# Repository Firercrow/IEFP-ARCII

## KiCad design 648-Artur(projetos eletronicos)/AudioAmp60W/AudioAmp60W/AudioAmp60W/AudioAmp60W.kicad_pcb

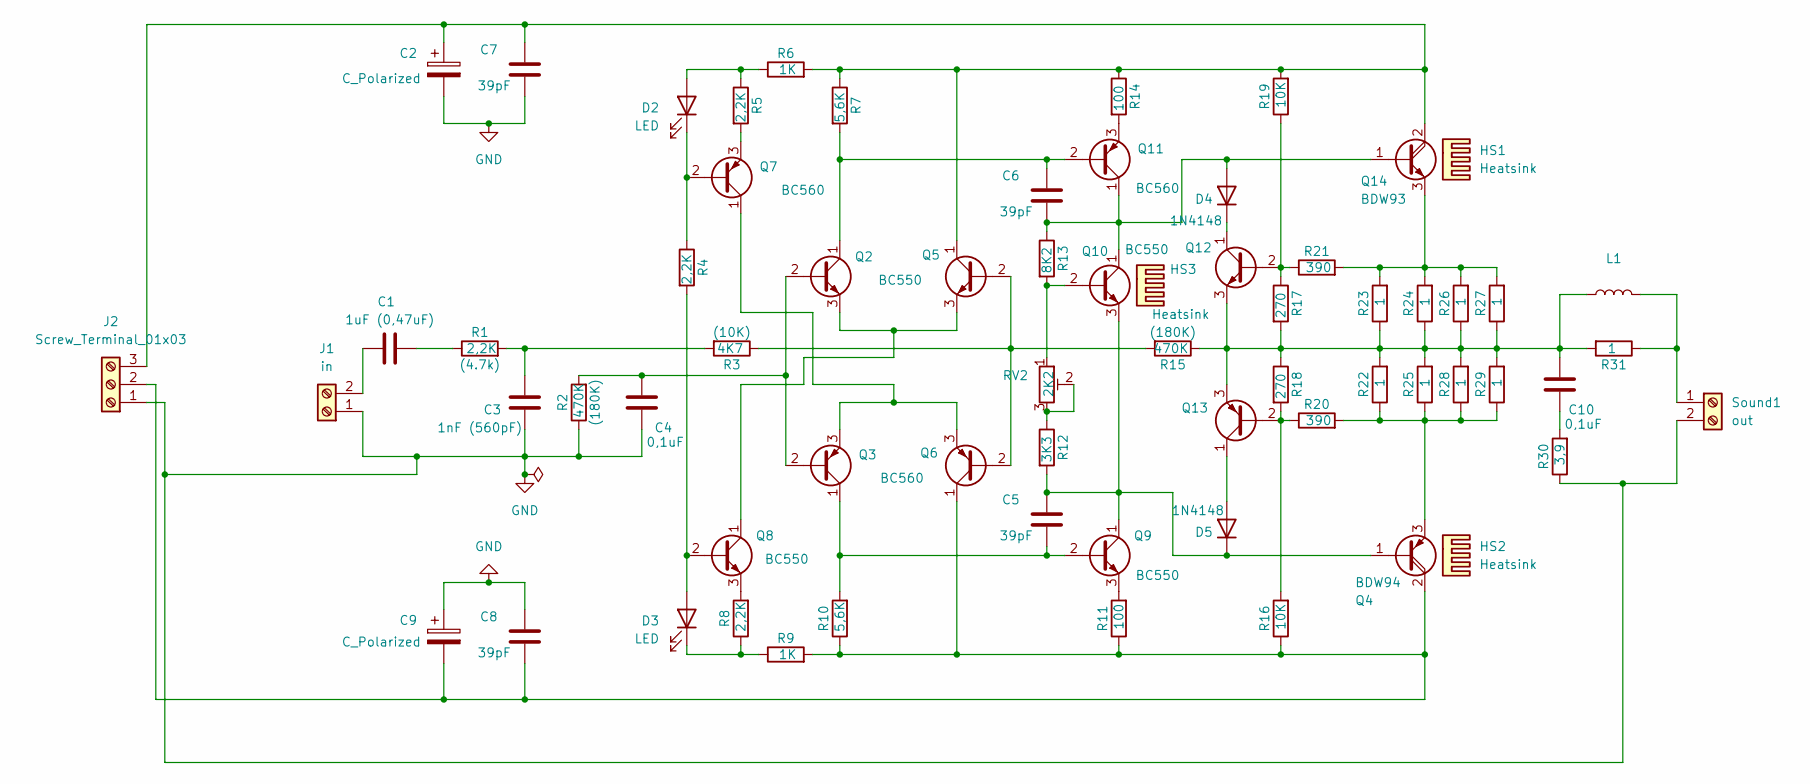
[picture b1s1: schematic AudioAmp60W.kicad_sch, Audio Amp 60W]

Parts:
C1: 1uF (0,47uF); C_Rect_L4.6mm_W2.0mm_P2.50mm_MKS02_FKP02
C2, C9: C_Polarized; CP_Radial_D4.0mm_P1.50mm
C3: 1nF (560pF); C_Rect_L4.6mm_W2.0mm_P2.50mm_MKS02_FKP02
C4, C10: 0,1uF; C_Rect_L4.6mm_W2.0mm_P2.50mm_MKS02_FKP02
C5, C6, C7, C8: 39pF; C_Rect_L4.6mm_W2.0mm_P2.50mm_MKS02_FKP02
D2, D3: LED; LED_Rectangular_W3.0mm_H2.0mm
D4, D5: 1N4148; D_DO-35_SOD27_P7.62mm_Horizontal
HS1, HS2, HS3: Heatsink
J1: in; TerminalBlock_Phoenix_MKDS-1-2-3.81_1x02_P3.81mm_Horizontal
J2: Screw_Terminal_01x03; TerminalBlock_Phoenix_MKDS-1-3-3.81_1x03_P3.81mm_Horizontal
L1: L_Axial_L7.0mm_D3.3mm_P10.16mm_Horizontal_Fastron_MICC
Q2, Q5, Q8, Q9, Q10, Q12: BC550; TO-92_Inline
Q3, Q6, Q7, Q11, Q13: BC560; TO-92_Inline
Q4: BDW94; TO-220-3_Vertical
Q14: BDW93; TO-220-3_Vertical
R1, R4, R5, R8: 2,2K; R_Axial_DIN0204_L3.6mm_D1.6mm_P7.62mm_Horizontal
R2, R15: 470K; R_Axial_DIN0204_L3.6mm_D1.6mm_P7.62mm_Horizontal
R3: 4K7; R_Axial_DIN0204_L3.6mm_D1.6mm_P7.62mm_Horizontal
R6, R9: 1K; R_Axial_DIN0204_L3.6mm_D1.6mm_P7.62mm_Horizontal
R7, R10: 5,6K; R_Axial_DIN0204_L3.6mm_D1.6mm_P7.62mm_Horizontal
R11, R14: 100; R_Axial_DIN0204_L3.6mm_D1.6mm_P7.62mm_Horizontal
R12: 3K3; R_Axial_DIN0204_L3.6mm_D1.6mm_P7.62mm_Horizontal
R13: 8K2; R_Axial_DIN0204_L3.6mm_D1.6mm_P7.62mm_Horizontal
R16, R19: 10K; R_Axial_DIN0204_L3.6mm_D1.6mm_P7.62mm_Horizontal
R17, R18: 270; R_Axial_DIN0204_L3.6mm_D1.6mm_P7.62mm_Horizontal
R20, R21: 390; R_Axial_DIN0204_L3.6mm_D1.6mm_P7.62mm_Horizontal
R22, R23, R24, R25, R26, R27, R28, R29, R31: 1; R_Axial_DIN0204_L3.6mm_D1.6mm_P7.62mm_Horizontal
R30: 3,9; R_Axial_DIN0204_L3.6mm_D1.6mm_P7.62mm_Horizontal
RV2: 2K2; Potentiometer_Bourns_3266W_Vertical
Sound1: out; TerminalBlock_Phoenix_MKDS-1-2-3.81_1x02_P3.81mm_Horizontal

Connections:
GND: C2.2, C3.2, C4.2, C7.2, C8.1, C9.1, J1.1, J2.1, R2.1, R30.1, Sound1.2
unnamed: C1.1, R1.1
unnamed: C3.1, R1.2, R3.2
unnamed: C10.2, R30.2
unnamed: D2.2 (A), R5.1, R6.1
unnamed: D2.1 (K), Q7.2 (B), R4.1
unnamed: D3.2 (A), Q8.2 (B), R4.2
unnamed: D3.1 (K), R8.1, R9.1
unnamed: C6.2, D4.2 (A), Q10.1 (C), Q11.1 (C), Q14.1 (B), R13.1
unnamed: D4.1 (K), Q12.1 (C)
unnamed: D5.2 (A), Q13.1 (C)
unnamed: C5.1, D5.1 (K), Q4.1 (B), Q9.1 (C), Q10.3 (E), R12.2
unnamed: C1.2, J1.2
unnamed: C8.2, C9.2, J2.2, Q4.2 (C), Q6.1 (C), R9.2, R10.1, R11.1, R16.1
unnamed: C2.1, C7.1, J2.3, Q5.1 (C), Q14.2 (C), R6.2, R7.1, R14.1, R19.2
unnamed: C4.1, Q2.2 (B), Q3.2 (B), R2.2
unnamed: Q2.3 (E), Q5.3 (E), Q8.1 (C)
unnamed: C5.2, Q3.1 (C), Q9.2 (B), R10.2
unnamed: Q3.3 (E), Q6.3 (E), Q7.1 (C)
unnamed: Q4.3 (E), R20.2, R22.1, R25.1, R28.1, R29.1
unnamed: Q5.2 (B), Q6.2 (B), R3.1, R15.2
unnamed: Q7.3 (E), R5.2
unnamed: Q8.3 (E), R8.2
unnamed: Q9.3 (E), R11.2
unnamed: Q10.2 (B), R13.2, RV2.1
unnamed: C6.1, Q2.1 (C), Q11.2 (B), R7.2
unnamed: Q11.3 (E), R14.2
unnamed: Q12.2 (B), R17.1, R19.1, R21.1
unnamed: C10.1, L1.1, Q12.3 (E), Q13.3 (E), R15.1, R17.2, R18.1, R22.2, R23.1, R24.1, R25.2, R26.1, R27.1, R28.2, R29.2, R31.2
unnamed: Q13.2 (B), R16.2, R18.2, R20.1
unnamed: Q14.3 (E), R21.2, R23.2, R24.2, R26.2, R27.2
unnamed: R12.1, RV2.2, RV2.3
unnamed: L1.2, R31.1, Sound1.1

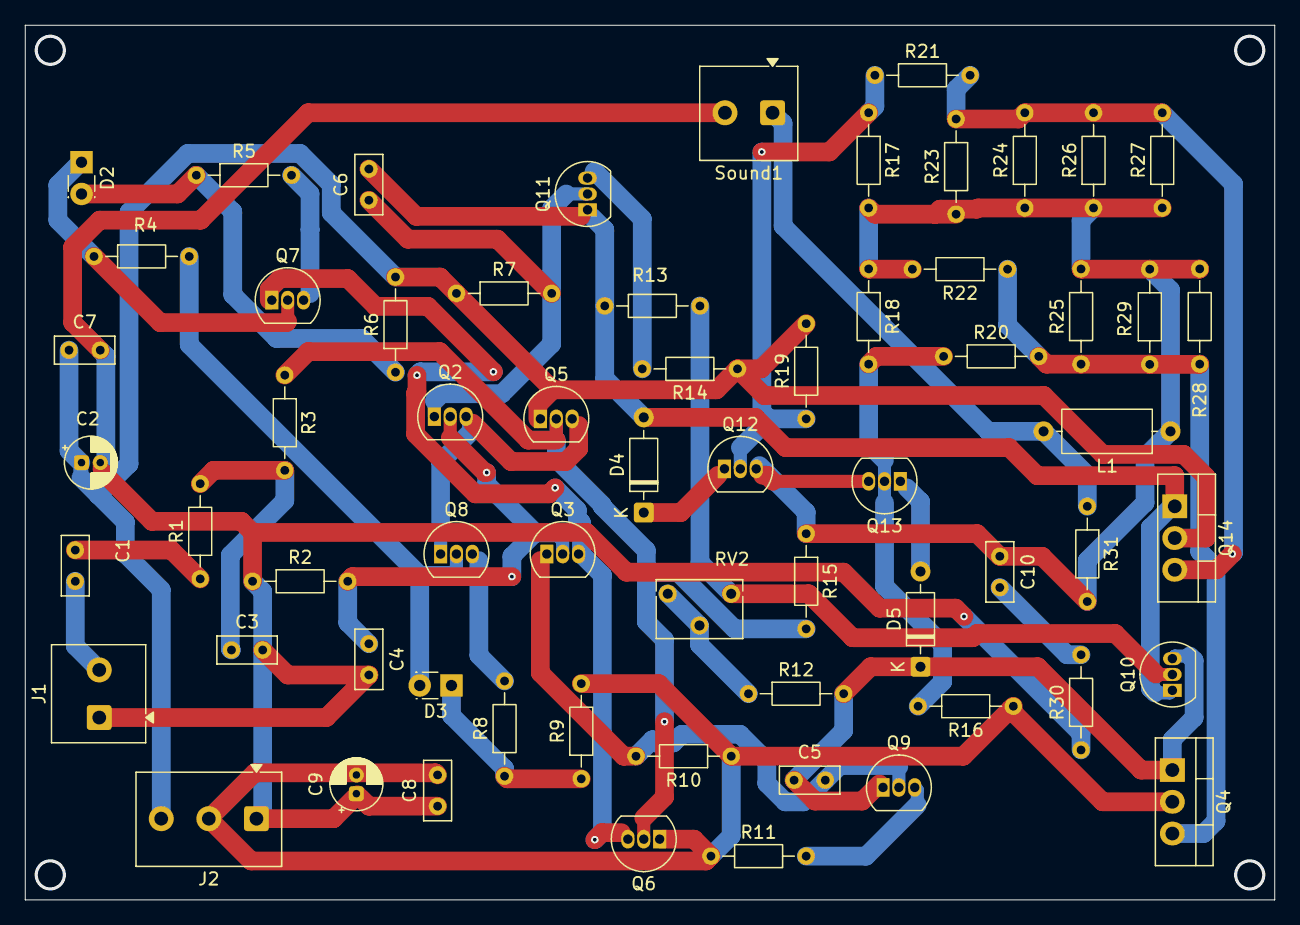
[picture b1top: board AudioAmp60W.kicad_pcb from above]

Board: 2 copper layers, 100.0 x 70.0 mm, 63 parts (0 on the bottom side), 33 nets.

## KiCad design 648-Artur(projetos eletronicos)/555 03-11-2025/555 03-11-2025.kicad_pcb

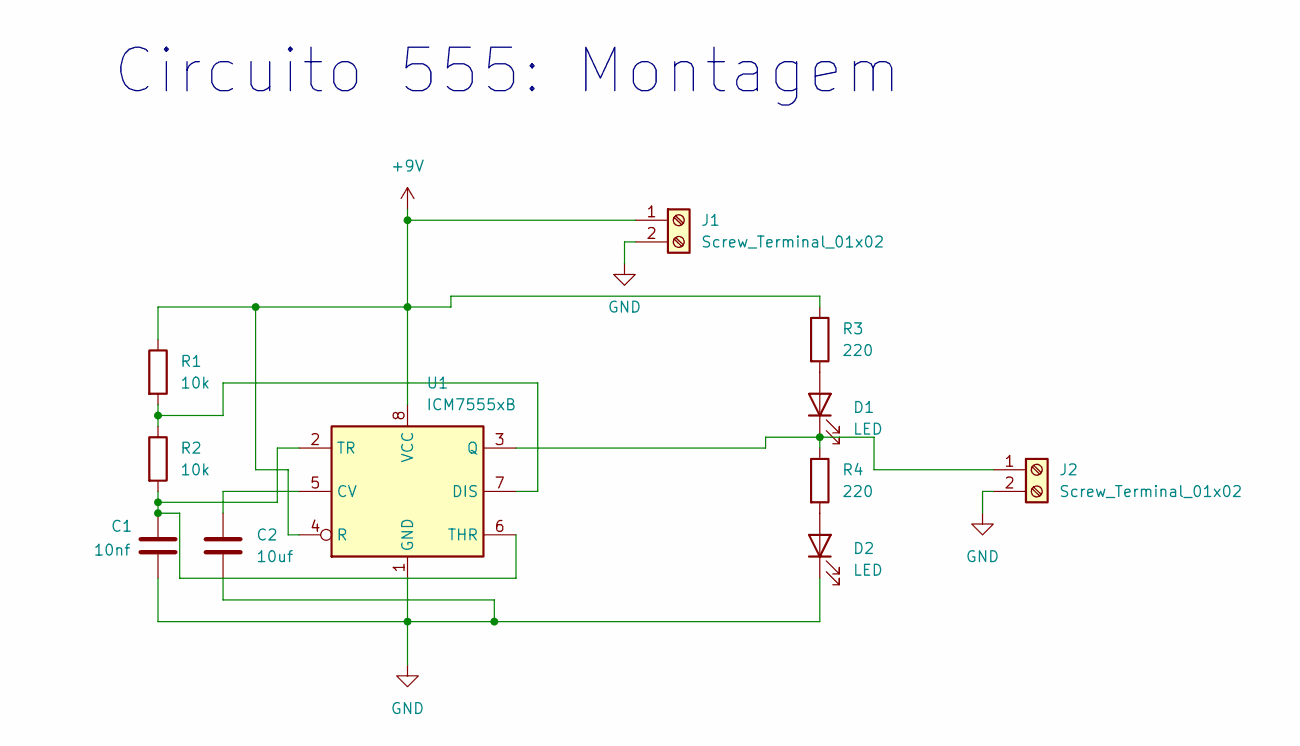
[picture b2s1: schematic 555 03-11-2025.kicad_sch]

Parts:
C1: 10nf; C_Radial_D4.0mm_H5.0mm_P1.50mm
C2: 10uf; C_Disc_D4.3mm_W1.9mm_P5.00mm
D1, D2: LED; LED_D3.0mm_Clear
J1, J2: Screw_Terminal_01x02; TerminalBlock_Philmore_TB132_1x02_P5.00mm_Horizontal
R1, R2: 10k; R_Axial_DIN0204_L3.6mm_D1.6mm_P5.08mm_Horizontal
R3, R4: 220; R_Axial_DIN0204_L3.6mm_D1.6mm_P7.62mm_Horizontal
U1: ICM7555xB; DIP-8_W7.62mm

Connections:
+9V: J1.1, R1.1, R3.1, U1.4 (R), U1.8 (VCC)
GND: C1.2, C2.2, D2.1 (K), J1.2, J2.2, U1.1 (GND)
unnamed: D1.2 (A), R3.2
unnamed: D1.1 (K), J2.1, R4.1, U1.3 (Q)
unnamed: D2.2 (A), R4.2
unnamed: C2.1, U1.5 (CV)
unnamed: R1.2, R2.1, U1.7 (DIS)
unnamed: C1.1, R2.2, U1.2 (TR), U1.6 (THR)

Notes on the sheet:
Circuito 555: Montagem

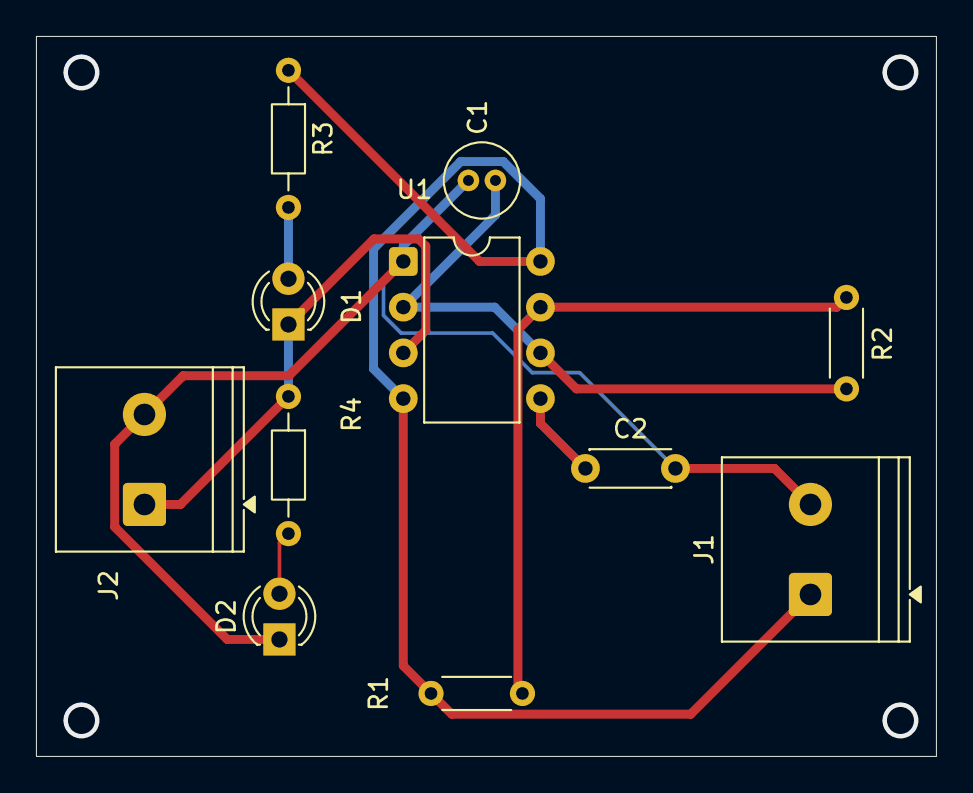
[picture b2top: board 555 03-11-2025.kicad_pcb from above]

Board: 2 copper layers, 50.0 x 40.0 mm, 11 parts (0 on the bottom side), 8 nets.

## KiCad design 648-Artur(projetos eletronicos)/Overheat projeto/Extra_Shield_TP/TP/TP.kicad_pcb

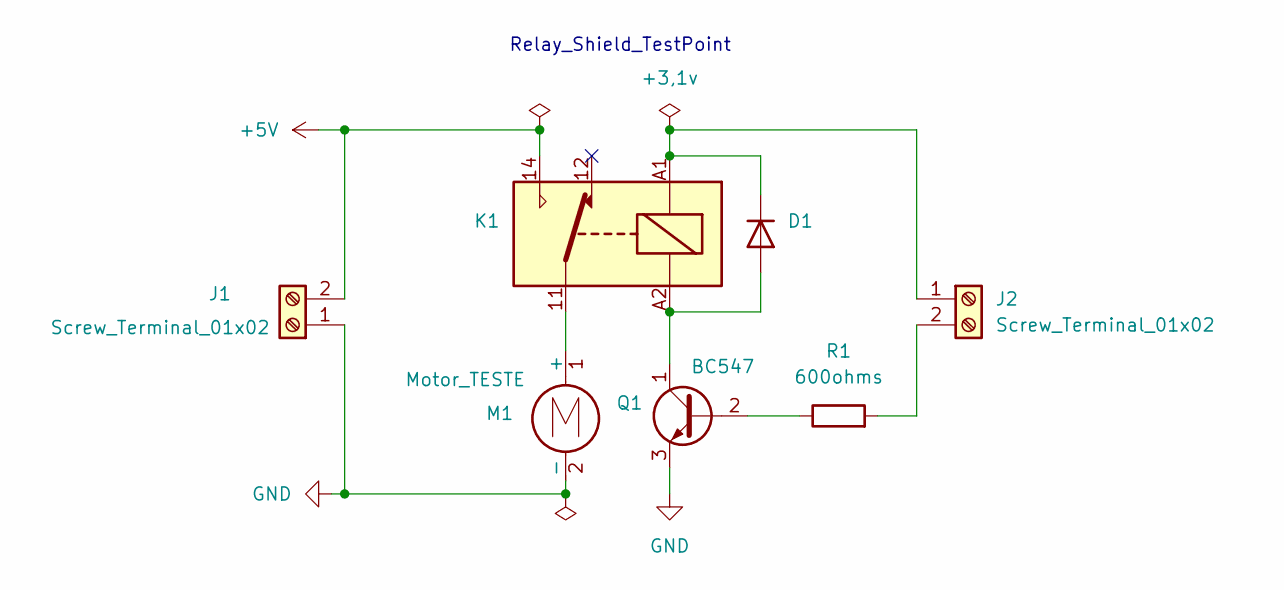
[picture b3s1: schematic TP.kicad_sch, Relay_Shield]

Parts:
D1: 1N4148WT; D_5W_P10.16mm_Horizontal
J1: Screw_Terminal_01x02; TerminalBlock_Phoenix_MKDS-1-2-3.81_1x02_P3.81mm_Horizontal
J2: Screw_Terminal_01x02; TerminalBlock_Phoenix_PT-1,5-2-3.5-H_1x02_P3.50mm_Horizontal
K1: Fujitsu_FTR-LYCA005x; Relay_SPDT_Schrack-RT1-FormC_RM5mm
M1: Motor_TESTE; TerminalBlock_Xinya_XY308-2.54-2P_1x02_P2.54mm_Horizontal
Q1: BC547; TO-92_Inline
R1: 600ohms; R_Axial_DIN0204_L3.6mm_D1.6mm_P5.08mm_Horizontal

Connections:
+5V: J1.2, K1.14
GND: J1.1, M1.2 (-), Q1.3 (E)
unnamed: D1.2 (A), K1.A2, Q1.1 (C)
unnamed: D1.1 (K), J2.1, K1.A1
unnamed: J2.2, R1.2
unnamed: K1.11, M1.1 (+)
unnamed: Q1.2 (B), R1.1

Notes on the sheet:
Relay_Shield_TestPoint

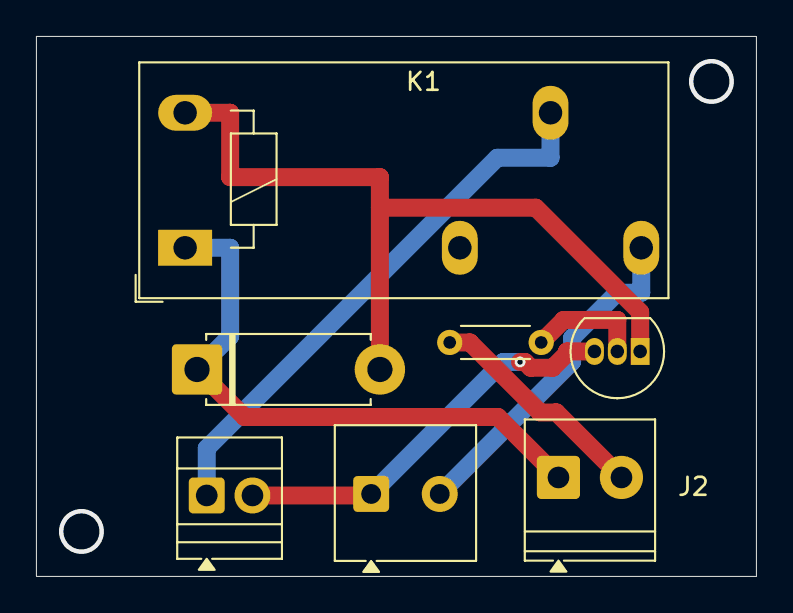
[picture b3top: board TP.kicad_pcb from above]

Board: 2 copper layers, 40.0 x 30.0 mm, 7 parts (0 on the bottom side), 7 nets.

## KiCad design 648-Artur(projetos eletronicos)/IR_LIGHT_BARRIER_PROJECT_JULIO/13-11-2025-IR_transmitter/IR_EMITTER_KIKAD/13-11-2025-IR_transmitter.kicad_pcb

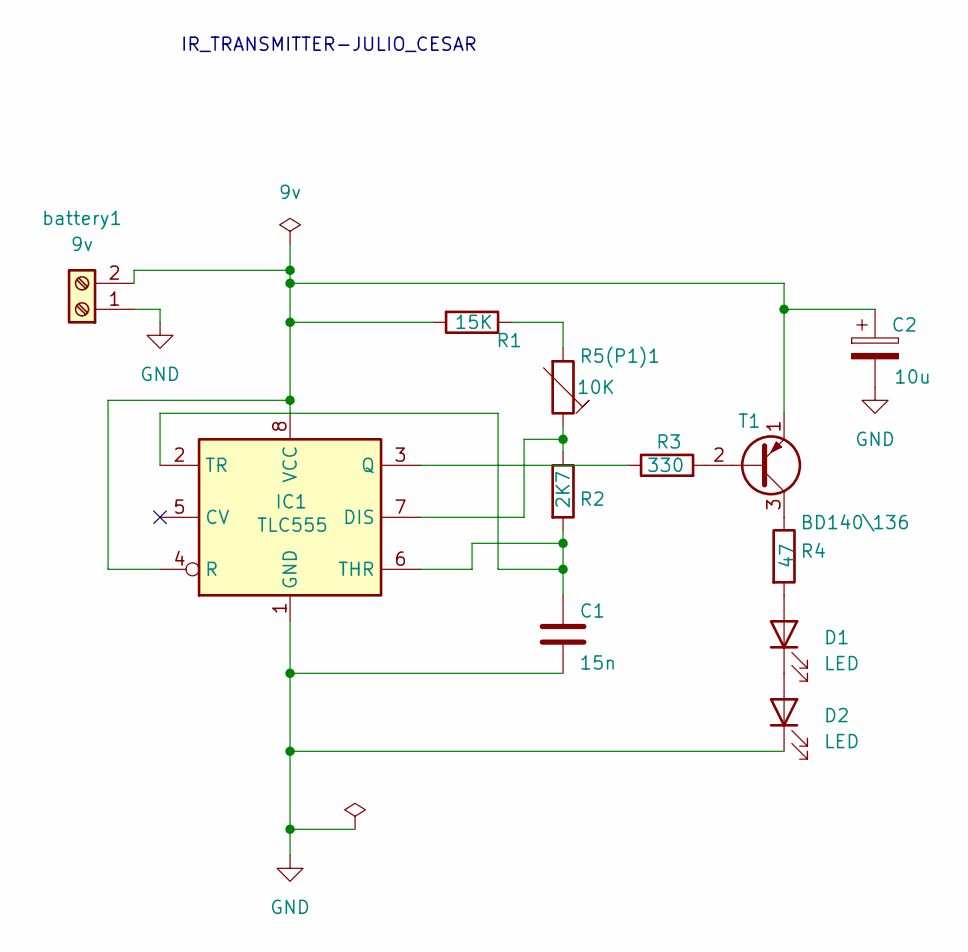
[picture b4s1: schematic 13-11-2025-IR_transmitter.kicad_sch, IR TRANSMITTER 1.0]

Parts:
C1: 15n; C_Rect_L4.0mm_W2.5mm_P2.50mm
C2: 10u; CP_Radial_D5.0mm_P2.50mm
D1, D2: LED; LED_D3.0mm
IC1: TLC555; DIP-8_W7.62mm
R1: 15K; R_Axial_DIN0204_L3.6mm_D1.6mm_P5.08mm_Horizontal
R2: 2K7; R_Axial_DIN0204_L3.6mm_D1.6mm_P5.08mm_Horizontal
R3: 330; R_Axial_DIN0204_L3.6mm_D1.6mm_P7.62mm_Horizontal
R4: 47; R_Axial_DIN0204_L3.6mm_D1.6mm_P5.08mm_Horizontal
R5(P1)1: 10K; R_Axial_DIN0204_L3.6mm_D1.6mm_P5.08mm_Horizontal
T1: BD140\136; TO-92_Inline
battery1: 9v; TerminalBlock_Phoenix_MPT-0,5-2-2.54_1x02_P2.54mm_Horizontal

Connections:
+9V: C2.1, IC1.4 (R), IC1.8 (VCC), R1.2, T1.1 (E), battery1.2
GND: C1.2, C2.2, D2.1 (K), IC1.1 (GND), battery1.1
unnamed: D1.2 (A), R4.2
unnamed: D1.1 (K), D2.2 (A)
unnamed: IC1.7 (DIS), R2.1, R5(P1)1.1
unnamed: IC1.3 (Q), R3.1
unnamed: C1.1, IC1.2 (TR), IC1.6 (THR), R2.2
unnamed: R1.1, R5(P1)1.2
unnamed: R3.2, T1.2 (B)
unnamed: R4.1, T1.3 (C)

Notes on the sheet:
IR_TRANSMITTER-JULIO_CESAR

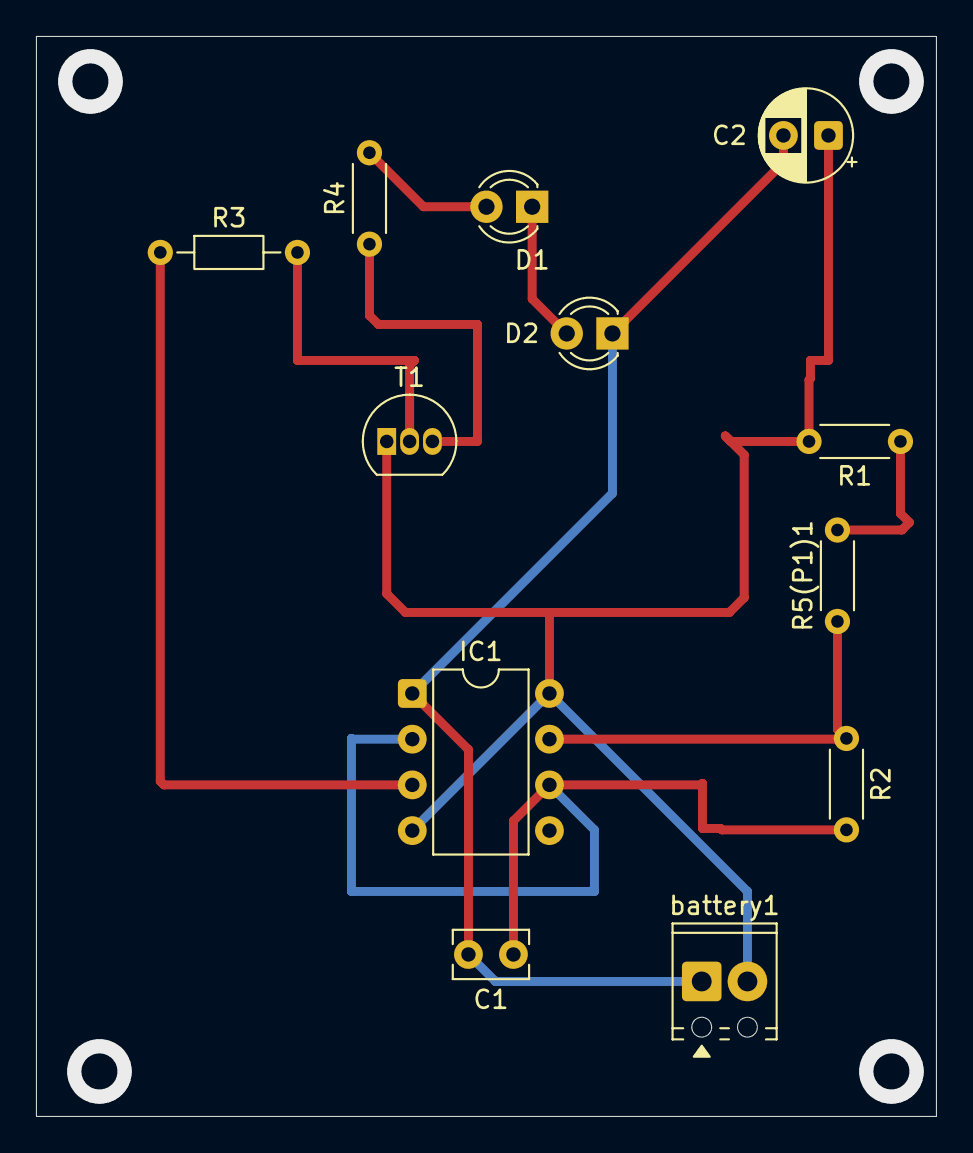
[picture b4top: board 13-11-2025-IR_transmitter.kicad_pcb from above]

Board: 2 copper layers, 50.0 x 60.0 mm, 12 parts (0 on the bottom side), 10 nets.

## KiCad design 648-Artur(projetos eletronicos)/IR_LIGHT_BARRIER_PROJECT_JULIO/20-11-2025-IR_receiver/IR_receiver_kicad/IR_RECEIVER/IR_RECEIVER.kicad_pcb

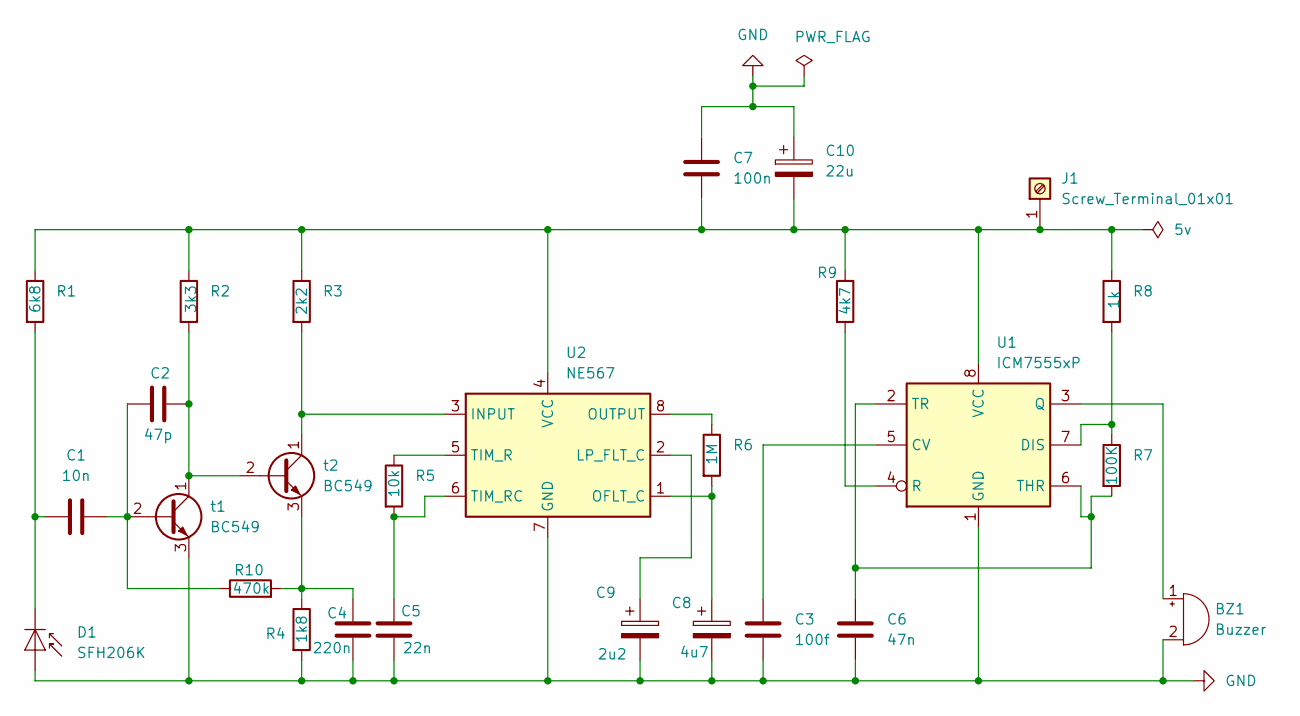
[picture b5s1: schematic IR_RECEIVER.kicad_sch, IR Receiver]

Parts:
BZ1: Buzzer; Buzzer_12x9.5RM7.6
C1: 10n; C_Rect_L4.6mm_W3.8mm_P2.50mm_MKS02_FKP02
C2: 47p; C_Rect_L4.6mm_W3.8mm_P2.50mm_MKS02_FKP02
C3: 100f; C_Rect_L4.6mm_W3.8mm_P2.50mm_MKS02_FKP02
C4: 220n; C_Rect_L4.6mm_W3.8mm_P2.50mm_MKS02_FKP02
C5: 22n; C_Rect_L4.6mm_W3.8mm_P2.50mm_MKS02_FKP02
C6: 47n; C_Rect_L4.6mm_W3.8mm_P2.50mm_MKS02_FKP02
C7: 100n; C_Rect_L4.6mm_W3.8mm_P2.50mm_MKS02_FKP02
C8: 4u7; CP_Radial_D4.0mm_P1.50mm
C9: 2u2; CP_Radial_D4.0mm_P1.50mm
C10: 22u; CP_Radial_D4.0mm_P1.50mm
D1: SFH206K; Osram_SFH205
J1: Screw_Terminal_01x01; TerminalBlock_MetzConnect_360272_1x01_Horizontal_ScrewM2.6
R1: 6k8; R_Axial_DIN0309_L9.0mm_D3.2mm_P12.70mm_Horizontal
R2: 3k3; R_Axial_DIN0309_L9.0mm_D3.2mm_P12.70mm_Horizontal
R3: 2k2; R_Axial_DIN0309_L9.0mm_D3.2mm_P12.70mm_Horizontal
R4: 1k8; R_Axial_DIN0309_L9.0mm_D3.2mm_P12.70mm_Horizontal
R5: 10k; R_Axial_DIN0309_L9.0mm_D3.2mm_P12.70mm_Horizontal
R6: 1M; R_Axial_DIN0309_L9.0mm_D3.2mm_P12.70mm_Horizontal
R7: 100K; R_Axial_DIN0309_L9.0mm_D3.2mm_P12.70mm_Horizontal
R8: 1k; R_Axial_DIN0309_L9.0mm_D3.2mm_P12.70mm_Horizontal
R9: 4k7; R_Axial_DIN0309_L9.0mm_D3.2mm_P12.70mm_Horizontal
R10: 470k; R_Axial_DIN0309_L9.0mm_D3.2mm_P12.70mm_Horizontal
U1: ICM7555xP; DIP-8_W7.62mm
U2: NE567; DIP-8_W7.62mm
t1, t2: BC549; TO-92_Inline

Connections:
GND: BZ1.2 (-), C3.2, C4.2, C5.2, C6.2, C7.1, C8.2, C9.2, C10.1, D1.2 (A), R4.2, U1.1 (GND), U2.7 (GND), t1.3 (E)
unnamed: BZ1.1 (+), U1.3 (Q)
unnamed: C1.1, D1.1 (K), R1.2
unnamed: C7.2, C10.2, J1.1, R1.1, R2.1, R3.1, R8.1, R9.1, U1.8 (VCC), U2.4 (VCC)
unnamed: C3.1, U1.5 (CV)
unnamed: R7.1, R8.2, U1.7 (DIS)
unnamed: R9.2, U1.4 (R)
unnamed: C6.1, R7.2, U1.2 (TR), U1.6 (THR)
unnamed: R3.2, U2.3 (INPUT), t2.1 (C)
unnamed: C9.1, U2.2 (LP_FLT_C)
unnamed: C8.1, R6.2, U2.1 (OFLT_C)
unnamed: R6.1, U2.8 (OUTPUT)
unnamed: R5.1, U2.5 (TIM_R)
unnamed: C5.1, R5.2, U2.6 (TIM_RC)
unnamed: C1.2, C2.2, R10.1, t1.2 (B)
unnamed: C2.1, R2.2, t1.1 (C), t2.2 (B)
unnamed: C4.1, R4.1, R10.2, t2.3 (E)

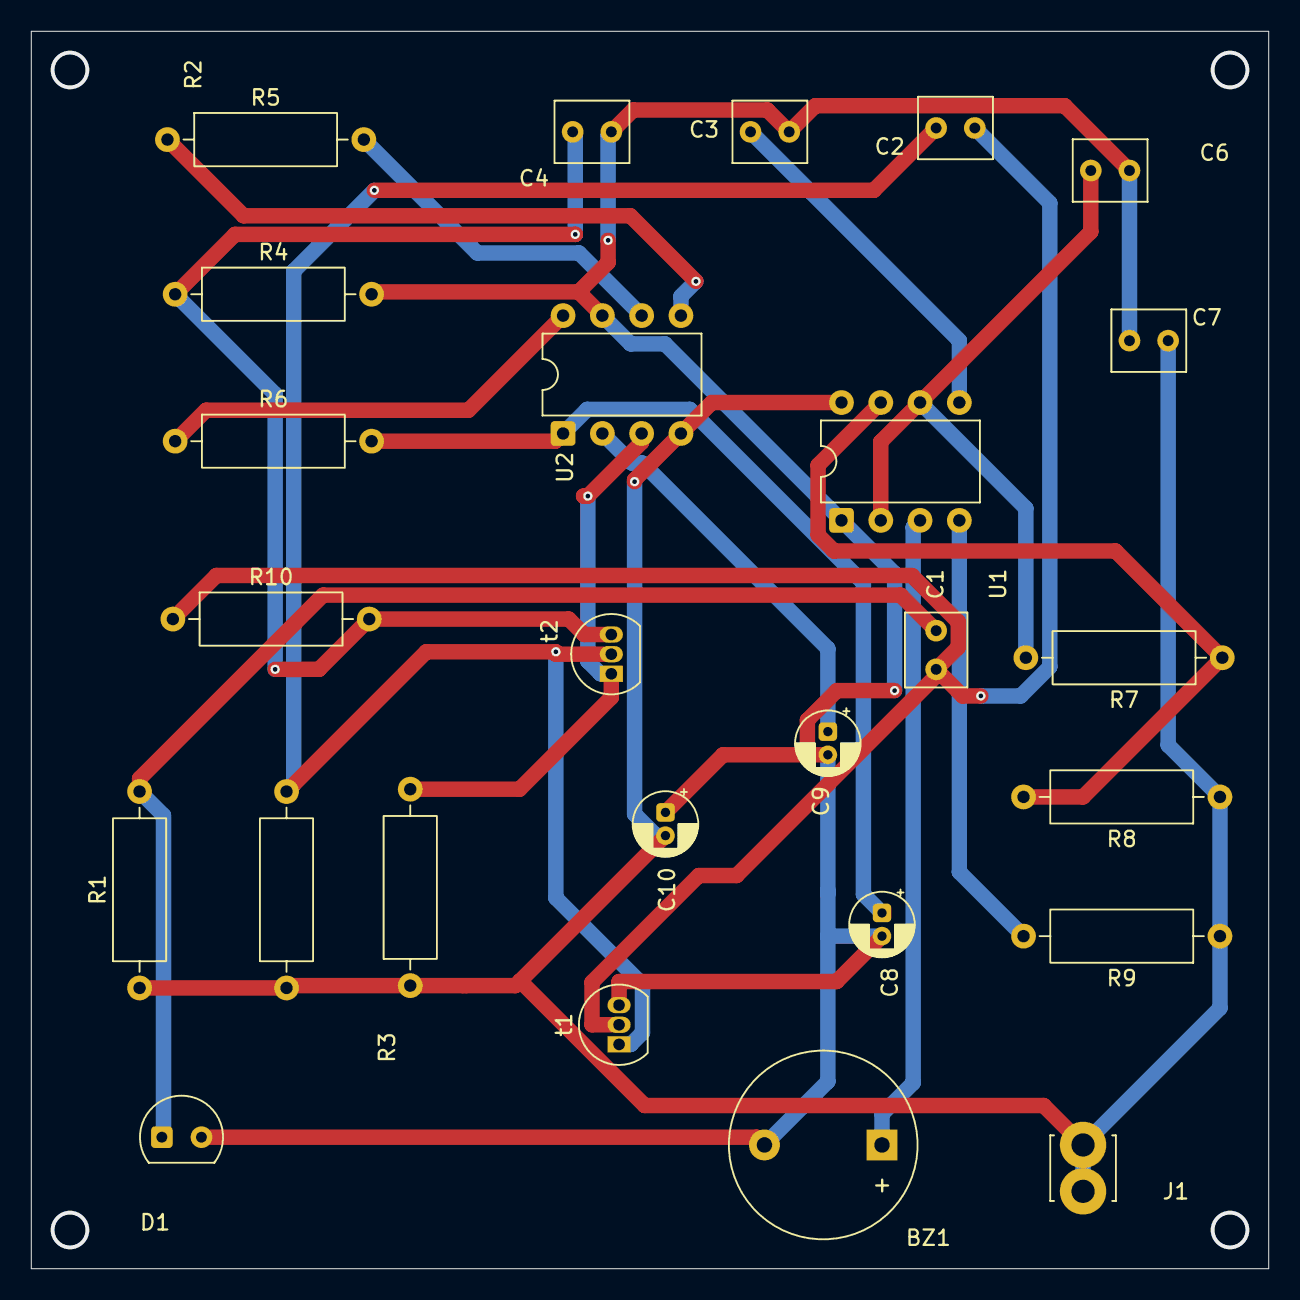
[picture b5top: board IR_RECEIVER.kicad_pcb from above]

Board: 2 copper layers, 80.0 x 80.0 mm, 26 parts (0 on the bottom side), 17 nets.

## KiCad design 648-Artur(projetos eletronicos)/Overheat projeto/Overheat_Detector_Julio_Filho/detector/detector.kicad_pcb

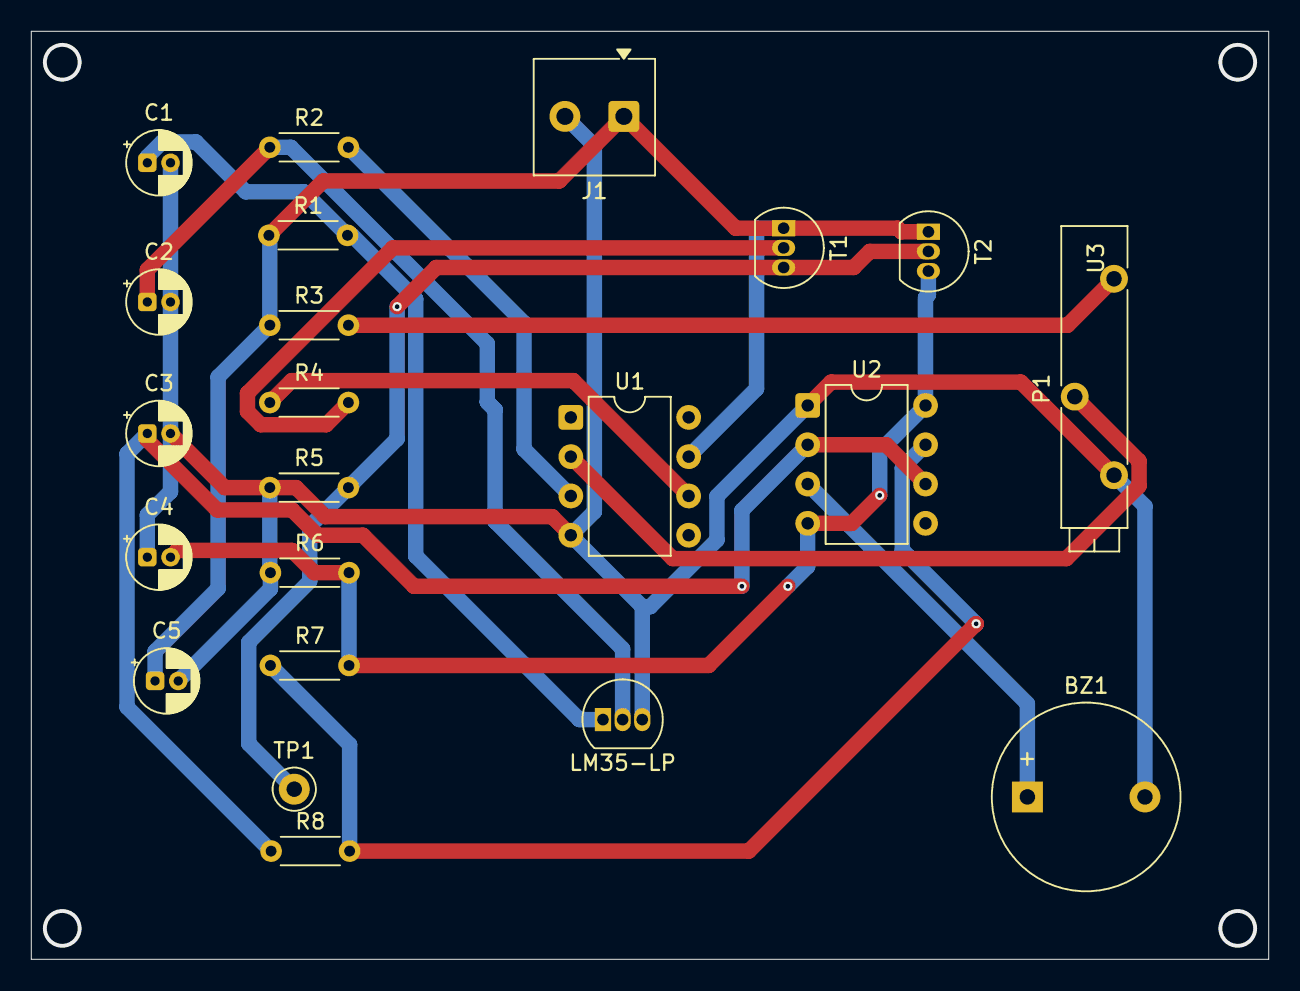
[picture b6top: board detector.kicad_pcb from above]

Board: 2 copper layers, 80.0 x 60.0 mm, 22 parts (0 on the bottom side), 14 nets.

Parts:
BZ1: 5v; Buzzer_12x9.5RM7.6
C1, C3: 10u; CP_Radial_D4.0mm_P1.50mm
C2: 1u; CP_Radial_D4.0mm_P1.50mm
C4: 47u; CP_Radial_D4.0mm_P1.50mm
C5: 100u; CP_Radial_D4.0mm_P1.50mm
J1: Screw_Terminal_01x02; TerminalBlock_Phoenix_MKDS-1-2-3.81_1x02_P3.81mm_Horizontal
P1: 10k; Potentiometer_Bourns_3005_Horizontal
R1: 1k; R_Axial_DIN0204_L3.6mm_D1.6mm_P5.08mm_Horizontal
R2: 12k; R_Axial_DIN0204_L3.6mm_D1.6mm_P5.08mm_Horizontal
R3: 10k; R_Axial_DIN0204_L3.6mm_D1.6mm_P5.08mm_Horizontal
R4: 12K; R_Axial_DIN0204_L3.6mm_D1.6mm_P5.08mm_Horizontal
R5: 2K2; R_Axial_DIN0204_L3.6mm_D1.6mm_P5.08mm_Horizontal
R6: 1M; R_Axial_DIN0204_L3.6mm_D1.6mm_P5.08mm_Horizontal
R7: 220K; R_Axial_DIN0204_L3.6mm_D1.6mm_P5.08mm_Horizontal
R8: 22K; R_Axial_DIN0204_L3.6mm_D1.6mm_P5.08mm_Horizontal
T1, T2: BC547; TO-92_Inline
TP1: TestPoint_Keystone_5000-5004_Miniature
U1: CA3130; DIP-8_W7.62mm
U2: NA555P; DIP-8_W7.62mm
U3: LM35-LP; TO-92_Inline

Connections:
GND: BZ1.2 (-), C1.2, C2.2, C3.2, C4.1, C5.2, J1.2, P1.3, R5.1, R6.1, U1.4 (V-), U2.1 (GND), U3.3 (GND)
unnamed: BZ1.1 (+), U2.3 (Q)
unnamed: C5.1, J1.1, R1.1, R3.1, T1.1 (C), T2.1 (C), U1.7 (V+)
unnamed: P1.1, R3.2
unnamed: R4.1, U1.6
unnamed: R4.2, T1.2 (B)
unnamed: R5.2, T1.3 (E), T2.2 (B), TP1.1
unnamed: C4.2, R6.2, R7.2, T2.3 (E), U2.4 (R), U2.8 (VCC)
unnamed: R2.2, U1.3 (+)
unnamed: P1.2, U1.2 (-)
unnamed: R7.1, R8.2, U2.7 (DIS)
unnamed: C3.1, R8.1, U2.2 (TR), U2.6 (THR)
unnamed: C1.1, R1.2, U3.1 (+V_{S})
unnamed: C2.1, R2.1, U3.2 (V_{OUT})

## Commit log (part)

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2026-01-28 Renomeei pasta de antiga para nova
